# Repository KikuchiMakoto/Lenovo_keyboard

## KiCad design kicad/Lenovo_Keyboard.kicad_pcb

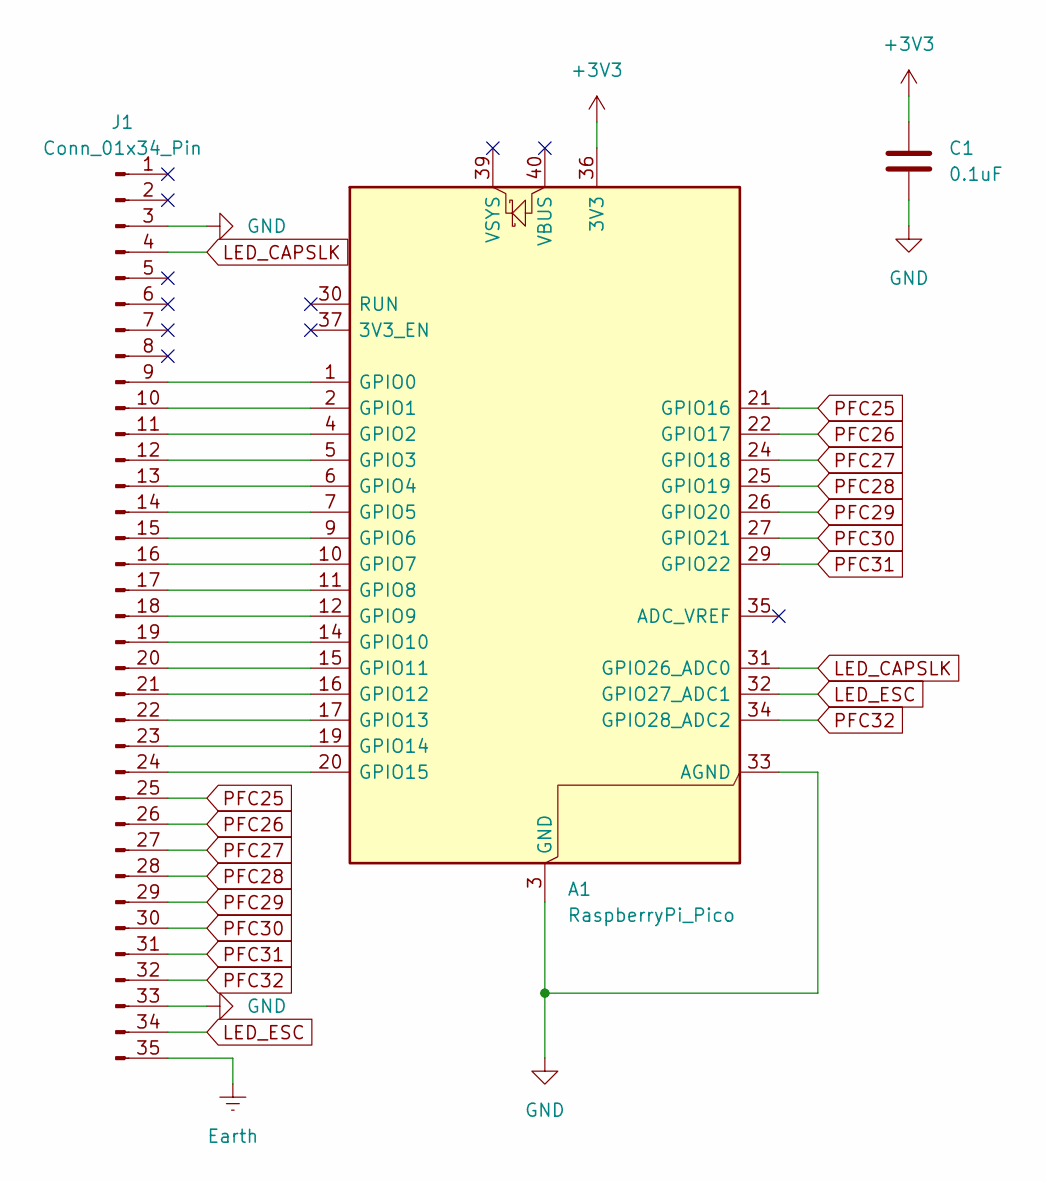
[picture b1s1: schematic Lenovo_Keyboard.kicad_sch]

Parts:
A1: RaspberryPi_Pico; RaspberryPi_Pico_Common_SMD
C1: 0.1uF; C_0805_2012Metric_Pad1.18x1.45mm_HandSolder
J1: Conn_01x34_Pin; FFC-PFC_0.8mm_34Pin

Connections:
+3V3: A1.36 (3V3), C1.1
Earth: J1.35
GND: A1.3 (GND), A1.8 (GND), A1.13 (GND), A1.18 (GND), A1.23 (GND), A1.28 (GND), A1.33 (AGND), A1.38 (GND), C1.2, J1.3, J1.33
LED_CAPSLK: A1.31 (GPIO26_ADC0), J1.4
LED_ESC: A1.32 (GPIO27_ADC1), J1.34
unnamed: A1.1 (GPIO0), J1.9
unnamed: A1.2 (GPIO1), J1.10
unnamed: A1.4 (GPIO2), J1.11
unnamed: A1.5 (GPIO3), J1.12
unnamed: A1.6 (GPIO4), J1.13
unnamed: A1.7 (GPIO5), J1.14
unnamed: A1.9 (GPIO6), J1.15
unnamed: A1.10 (GPIO7), J1.16
unnamed: A1.11 (GPIO8), J1.17
unnamed: A1.12 (GPIO9), J1.18
unnamed: A1.14 (GPIO10), J1.19
unnamed: A1.15 (GPIO11), J1.20
unnamed: A1.16 (GPIO12), J1.21
unnamed: A1.17 (GPIO13), J1.22
unnamed: A1.19 (GPIO14), J1.23
unnamed: A1.20 (GPIO15), J1.24
PFC25: A1.21 (GPIO16), J1.25
PFC26: A1.22 (GPIO17), J1.26
PFC27: A1.24 (GPIO18), J1.27
PFC28: A1.25 (GPIO19), J1.28
PFC29: A1.26 (GPIO20), J1.29
PFC30: A1.27 (GPIO21), J1.30
PFC31: A1.29 (GPIO22), J1.31
PFC32: A1.34 (GPIO28_ADC2), J1.32

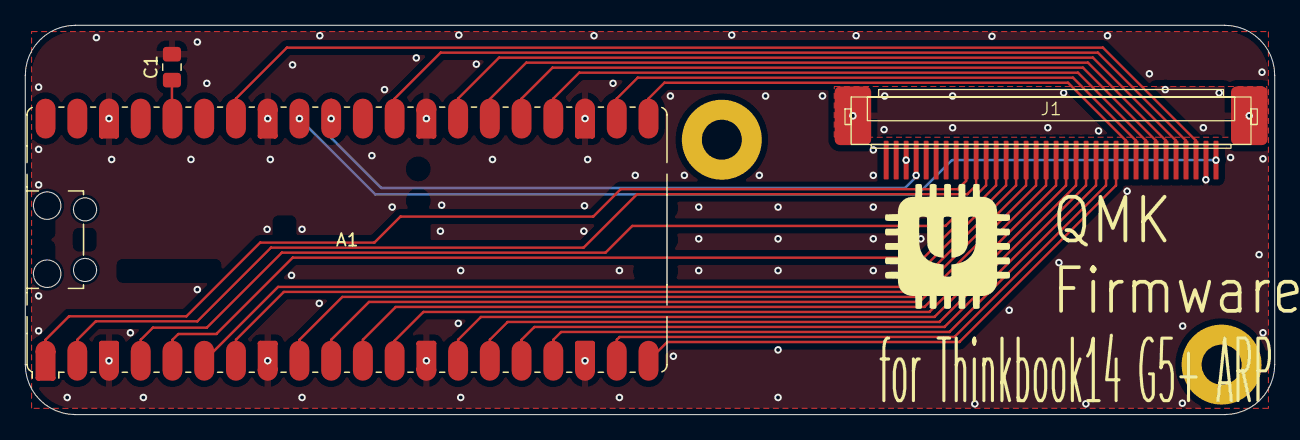
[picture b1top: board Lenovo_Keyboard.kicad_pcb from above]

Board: 2 copper layers, 100.0 x 31.2 mm, 3 parts (0 on the bottom side), 28 nets.

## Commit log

2025-09-08 2025/09/08 fab version
2025-09-09 SOIC-16 version
2025-09-09 SOP-16 version
2025-09-17 fix keymap typo & add VIA support format keyboad layout
2025-09-17 Update lib & name
2025-09-28 update project
2025-09-28 CapsLk/Escape LED support
